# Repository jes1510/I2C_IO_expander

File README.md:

# I2C_IO_expander

Designed by Jesse Merritt www.github.com/jes1510 December 2, 2015

This design is free software: you can redistribute it and/or modify it under the terms of the GNU General Public License as published by the Free Software Foundation, either version 3 of the License, or (at your option) any later version.

This program is distributed in the hope that it will be useful, but WITHOUT ANY WARRANTY; without even the implied warranty of MERCHANTABILITY or FITNESS FOR A PARTICULAR PURPOSE. See the GNU General Public License for more details.

You should have received a copy of the GNU General Public License along with this program. If not, see <http://www.gnu.org/licenses/

This is an I2C IO expander board that will add 16 pins of IO to a micro controller over I2C.  The IC used allows up to 8 devices on a bus so they can be daisy chained using common RJ11 (telephone) patch cables, allowing a max of 128 pins of IO.  The address is configurable along with terminations and interrupt destinations.

You can assume that I have no idea what I am doing and therefor am not responsible for any damage or negative consequences for using anything from this project. It may destroy all of your equipment and burn down your house.

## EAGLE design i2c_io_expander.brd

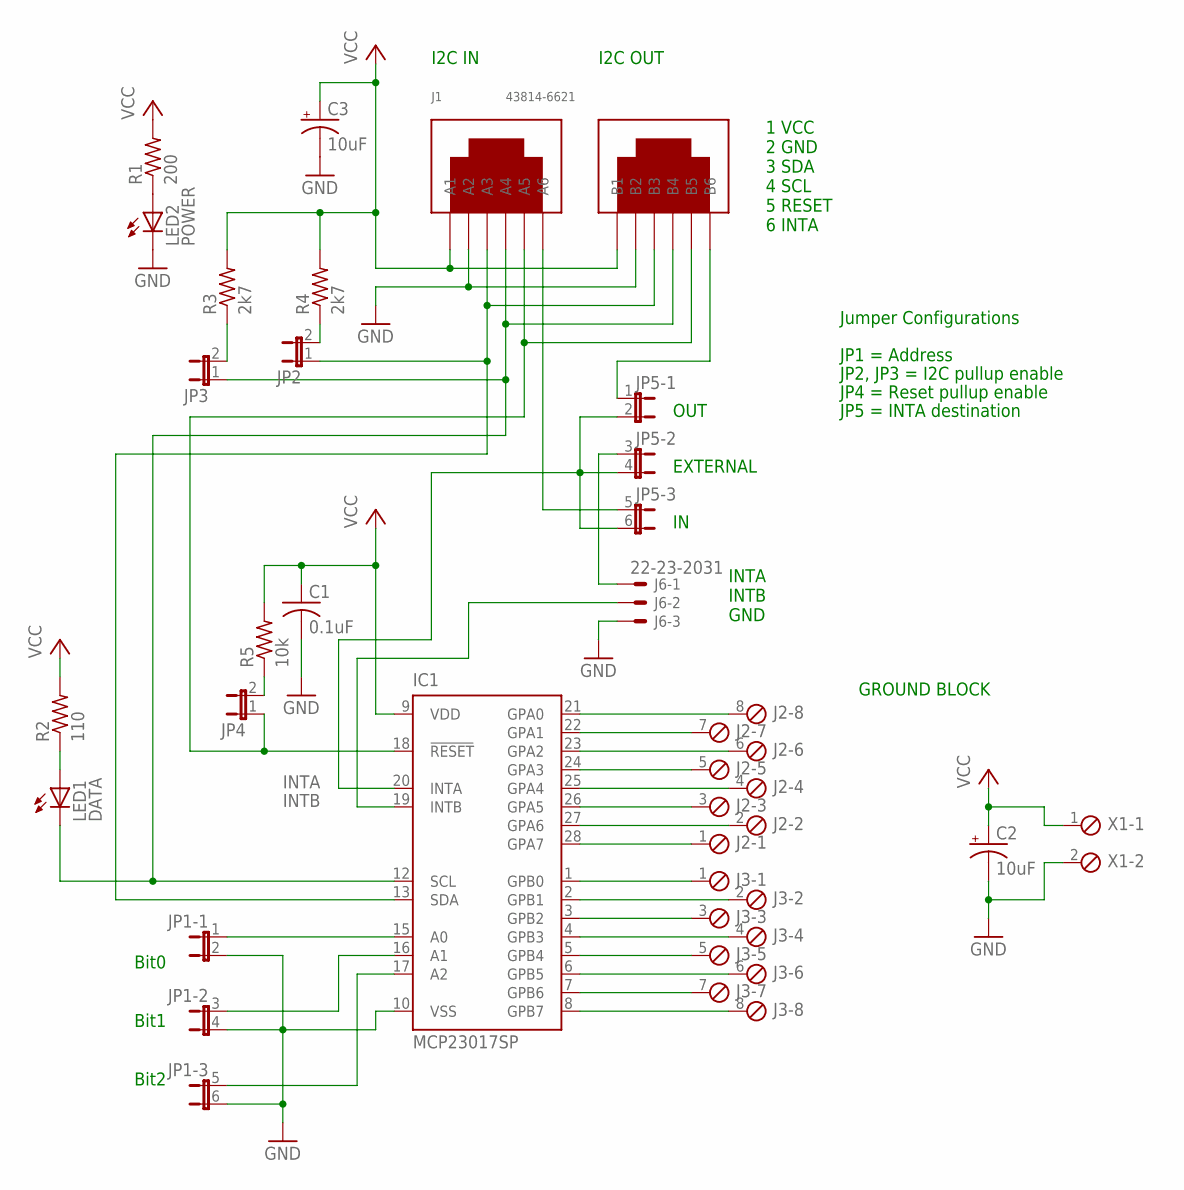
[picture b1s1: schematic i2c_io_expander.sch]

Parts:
C1: 0.1uF; C025-025X050
C2, C3: 10uF; E5-6
IC1: MCP23017SP; DIL28-3
J1: 43814-6621; MPN 43814-6621
J2, J3: MPT8; 8POL254; MPN 1725711
J6: 22-23-2031
JP1, JP5: JP3QE; JP3Q
JP2, JP3, JP4: JP1E; JP1
LED1: DATA; SMARTLED-TTW
LED2: POWER; SMARTLED-TTW
R1: 200; R0603
R2: 110; R0603
R3, R4: 2k7; R0603
R5: 10k; R0603
X1: MPT2; 2POL254

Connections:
GND: C1.2, C2.-, C3.-, IC1.10 (VSS), J1.A2, J1.B2, J6.3, JP1.2, JP1.4 (2), JP1.6 (2), LED2.C@1 (C), X1.2
INTA: IC1.20 (INTA), JP5.2, JP5.4 (2), JP5.6 (2)
INTB: IC1.19 (INTB), J6.2
unnamed: IC1.15 (A0), JP1.1
unnamed: IC1.16 (A1), JP1.3 (1)
unnamed: IC1.17 (A2), JP1.5 (1)
unnamed: LED2.A@1 (A), R1.1
unnamed: J1.B6, JP5.1
unnamed: JP3.2, R3.1
unnamed: JP4.2, R5.1
unnamed: J6.1, JP5.3 (1)
unnamed: JP2.2, R4.1
unnamed: LED1.A@1 (A), R2.1
unnamed: IC1.28 (GPA7), J2.1
unnamed: IC1.27 (GPA6), J2.2
unnamed: IC1.26 (GPA5), J2.3
unnamed: J1.A6, JP5.5 (1)
unnamed: IC1.25 (GPA4), J2.4
unnamed: IC1.24 (GPA3), J2.5
unnamed: IC1.23 (GPA2), J2.6
unnamed: IC1.22 (GPA1), J2.7
unnamed: IC1.21 (GPA0), J2.8
unnamed: IC1.1 (GPB0), J3.1
unnamed: IC1.2 (GPB1), J3.2
unnamed: IC1.3 (GPB2), J3.3
unnamed: IC1.4 (GPB3), J3.4
unnamed: IC1.5 (GPB4), J3.5
unnamed: IC1.6 (GPB5), J3.6
unnamed: IC1.7 (GPB6), J3.7
unnamed: IC1.8 (GPB7), J3.8
RESET: IC1.18 (!RESET), J1.A5, J1.B5, JP4.1
SCL: IC1.12 (SCL), J1.A4, J1.B4, JP3.1, LED1.C@1 (C)
SDA: IC1.13 (SDA), J1.A3, J1.B3, JP2.1
VCC: C1.1, C2.+, C3.+, IC1.9 (VDD), J1.A1, J1.B1, R1.2, R2.2, R3.2, R4.2, R5.2, X1.1

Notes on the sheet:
JP4 = Reset pullup enable
1 VCC 2 GND 3 SDA 4 SCL 5 RESET 6 INTA
I2C IN
I2C OUT
OUT
EXTERNAL
JP2, JP3 = I2C pullup enable
JP1 = Address
JP5 = INTA destination
Jumper Configurations
INTA INTB GND
Bit0 Bit1 Bit2
GROUND BLOCK

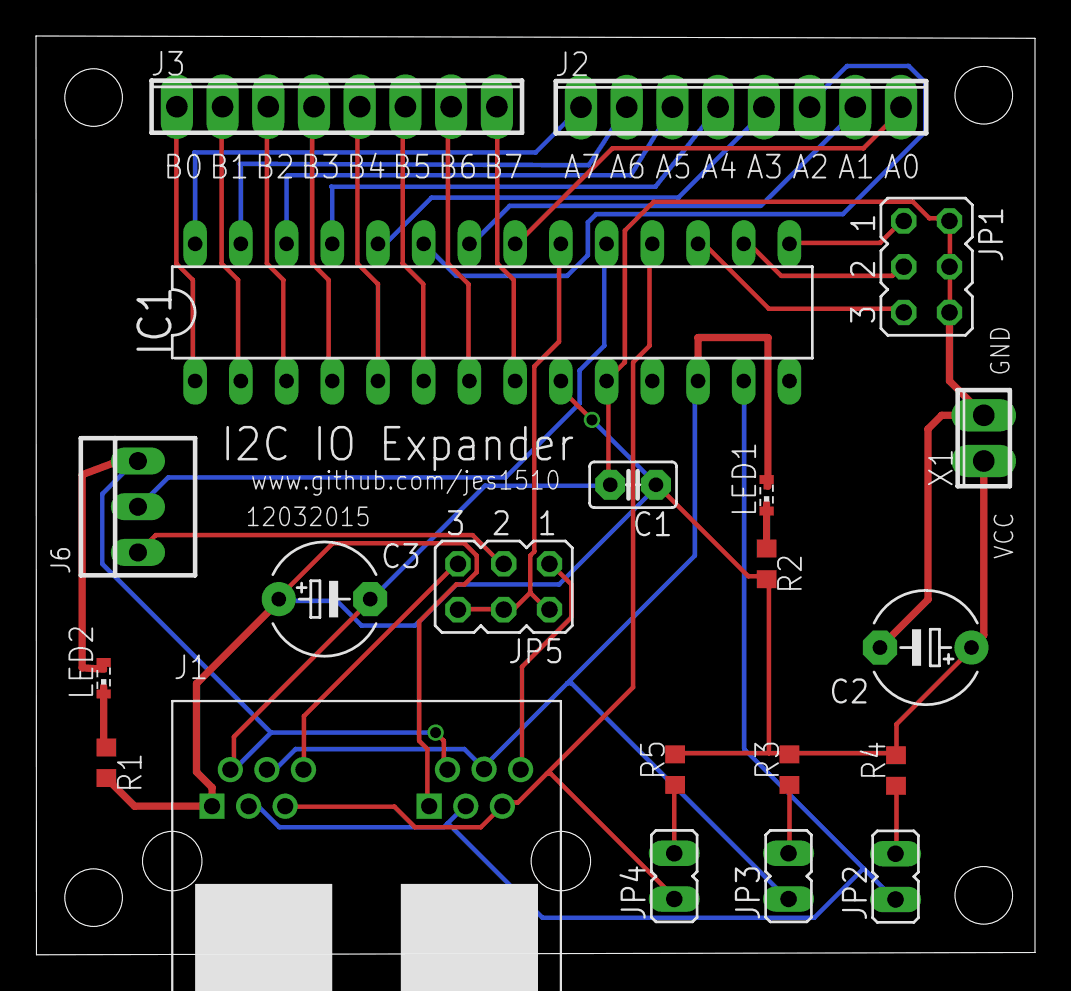
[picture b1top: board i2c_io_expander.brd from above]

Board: 2 copper layers, 55.5 x 51.0 mm, 21 parts (0 on the bottom side), 34 nets.

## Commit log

2015-12-03 Removed the gerb274x.cam file that was accidentally included in initial commit
2015-12-03 Added contact info and rev # to silkscreen Added VCC and GND designator to silkscreen
2015-12-05 added RJ11 datasheet
2015-12-27 Added title block Added additional text to claify jumper settings
